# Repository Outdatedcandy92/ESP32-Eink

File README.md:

# ESP32 E-INK Board

A tiny E-Ink display driver board featuring an ESP32-C3 and an onboard battery charging IC. It wirelessly drives a 2.13-inch E-Ink display and is designed for portable, ultra-low-power projects such as status displays, or dashboards.

---
## Schematic

---
## PCB

---
## BOM

| Name                                                                                                                                                               | Description                                                           | Quantity | Price      | Shipping   |
| ------------------------------------------------------------------------------------------------------------------------------------------------------------------ | --------------------------------------------------------------------- | -------- | ---------- | ---------- |
| PCB & Stencil                                                                                                                                                      | PCB & Stencil from JLCPCB                                             | -        | $10.10     | $8.47      |
| Componenets                                                                                                                                                        | Components from LCSC. Detailed breakdown [here](./production/bom.csv) | -        | $25.72     | $13.75     |
| [E-Ink Display](https://www.alibaba.com/product-detail/E-paper-Technology-2-13-Inch_1601018719280.html?spm=a2700.product_home_fy25.home_header.132.2ce267af3jYzDY) | E-Ink Display from Alibaba                                            | 1        | $6.76      | $9.66      |
| Sub Total                                                                                                                                                          |                                                                       |          | **$42.58** | **$31.88** |
| Total                                                                                                                                                              |                                                                       |          | **$74.46** |            |

---

## License

This project is licensed under the CERN Open Hardware Licence Version 2 Weakly Reciprocal [(CERN OHL W)](LICENSE.txt)

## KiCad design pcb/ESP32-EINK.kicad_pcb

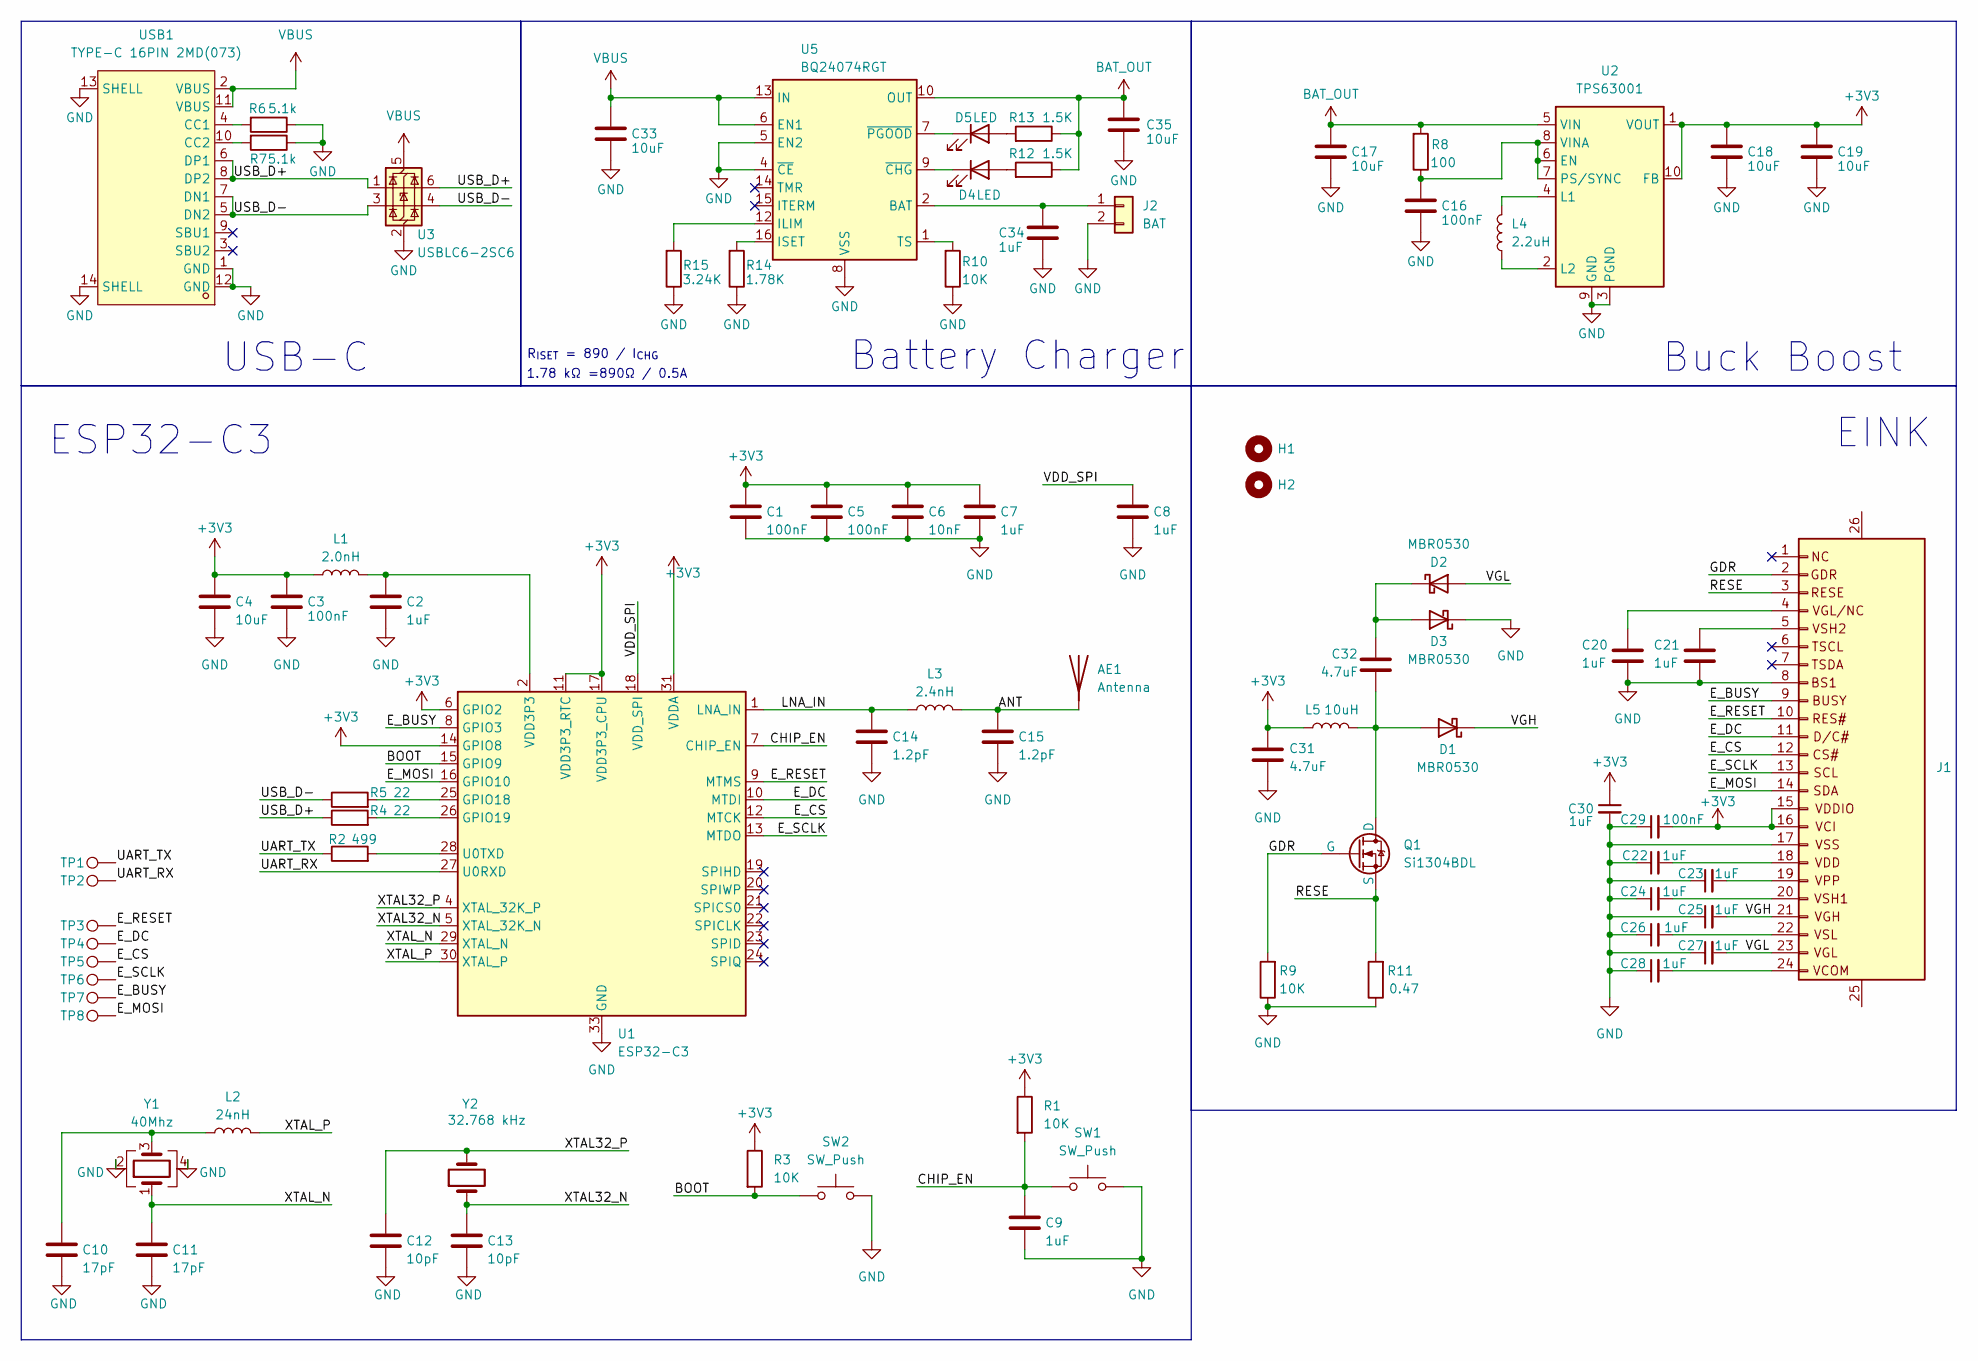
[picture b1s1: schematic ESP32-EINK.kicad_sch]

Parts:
AE1: Antenna; Johanson_2450AT18x100; LCSC Part C89334
C1, C3, C5, C16, C29: 100nF; C_0402_1005Metric; LCSC Part C1525
C2, C7, C8, C9, C20, C21, C22, C23, C24, C25, C26, C27, C28, C30, C34: 1uF; C_0402_1005Metric; LCSC Part C52923
C4, C17, C18, C19, C33, C35: 10uF; C_0402_1005Metric; LCSC Part C315248
C6: 10nF; C_0402_1005Metric; LCSC Part C15195
C10, C11: 17pF; C_0402_1005Metric; LCSC Part C1517782
C12, C13: 10pF; C_0402_1005Metric; LCSC Part C76946
C14, C15: 1.2pF; C_0201_0603Metric; LCSC Part C85895
C31, C32: 4.7uF; C_0402_1005Metric; LCSC Part C23733
D1, D2, D3: MBR0530; D_SOD-123; LCSC Part C82046
D4, D5: LED; LED_0402_1005Metric; LCSC Part C30584803
H1, H2: MountingHole; MountingHole_2.2mm_M2
J1: Conn_01x26; FPC-SMD_24P-P0.50_05B20U24P; LCSC Part C5362165
J2: BAT; JST_SH_BM02B-SRSS-TB_1x02-1MP_P1.00mm_Vertical; LCSC Part C160402
L1: 2.0nH; L_0402_1005Metric; LCSC Part C2986275
L2: 24nH; L_0402_1005Metric; LCSC Part C167472
L3: 2.4nH; L_0201_0603Metric; LCSC Part C2043647
L4: 2.2uH; L_1008_2520Metric; LCSC Part C1333325
L5: 10uH; IND-SMD_L4.0-W4.0_FNR40XXS; LCSC Part C167879
Q1: Si1304BDL; SOT-323_SC-70; LCSC Part C7419947
R1, R3, R9, R10: 10K; R_0402_1005Metric; LCSC Part C25531
R2: 499; R_0402_1005Metric; LCSC Part C4125
R4, R5: 22; R_0402_1005Metric; LCSC Part C25092
R6, R7: 5.1k; R_0402_1005Metric; LCSC Part C25905
R8: 100; R_0402_1005Metric; LCSC Part C25076
R11: 0.47; R_0402_1005Metric; LCSC Part C2771738
R12, R13: 1.5K; R_0402_1005Metric; LCSC Part C25867
R14: 1.78K; R_0402_1005Metric; LCSC Part C113478
R15: 3.24K; R_0402_1005Metric; LCSC Part C11457
SW1, SW2: SW_Push; SW-SMD_L3.9-W3.0-P4.45; LCSC Part C720477
TP1, TP2, TP3, TP4, TP5, TP6, TP7, TP8: TestPoint; TestPoint_Keystone_5000-5004_Miniature; LCSC Part C5199802
U1: ESP32-C3; QFN-32-1EP_5x5mm_P0.5mm_EP3.7x3.7mm; LCSC Part C2858491
U2: TPS63001; Texas_DRC0010J_ThermalVias; LCSC Part C28060
U3: USBLC6-2SC6; SOT-23-6; LCSC Part C7519
U5: BQ24074RGT; VQFN-16-1EP_3x3mm_P0.5mm_EP1.6x1.6mm; LCSC Part C54313
USB1: TYPE-C 16PIN 2MD(073); USB-C-SMD_TYPE-C-6PIN-2MD-073; LCSC Part C2765186
Y1: 40Mhz; Crystal_SMD_2016-4Pin_2.0x1.6mm; LCSC Part C255898
Y2: 32.768 kHz; Crystal_SMD_2012-2Pin_2.0x1.2mm; LCSC Part C99009

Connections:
+3V3: C1.1, C3.1, C4.1, C5.1, C6.1, C7.1, C18.1, C19.1, C29.2, C30.1, C31.1, J1.15, J1.16, L1.1, L5.1, R1.1, R3.1, U1.6 (GPIO2), U1.11 (VDD3P3_RTC), U1.14 (GPIO8), U1.17 (VDD3P3_CPU), U1.31 (VDDA), U1.32 (VDDA), U2.1 (VOUT), U2.10 (FB)
/ANT: AE1.1 (A), C15.1, L3.2
/BOOT: R3.2, SW2.1, U1.15 (GPIO9)
/CHIP_EN: C9.1, R1.2, SW1.1, U1.7 (CHIP_EN)
/E_BUSY: J1.9, TP7.1, U1.8 (GPIO3)
/E_CS: J1.12, TP5.1, U1.12 (MTCK)
/E_DC: J1.11, TP4.1, U1.10 (MTDI)
/E_MOSI: J1.14, TP8.1, U1.16 (GPIO10)
/E_RESET: J1.10, TP3.1, U1.9 (MTMS)
/E_SCLK: J1.13, TP6.1, U1.13 (MTDO)
/GDR: J1.2, Q1.2 (G), R9.2
/LNA_IN: C14.1, L3.1, U1.1 (LNA_IN)
/RESE: J1.3, Q1.3 (S), R11.2
/UART_RX: TP2.1, U1.27 (U0RXD)
/UART_TX: R2.1, TP1.1
/USB_D+: R4.1, U3.1 (I/O1), U3.6 (I/O1), USB1.6 (DP1), USB1.8 (DP2)
/USB_D-: R5.1, U3.3 (I/O2), U3.4 (I/O2), USB1.5 (DN2), USB1.7 (DN1)
/VDD_SPI: C8.1, U1.18 (VDD_SPI)
/VGH: C25.2, D1.1 (K), J1.21
/VGL: C27.2, D2.2 (A), J1.23
/XTAL32_N: C13.1, U1.5 (XTAL_32K_N), Y2.1
/XTAL32_P: C12.1, U1.4 (XTAL_32K_P), Y2.2
/XTAL_N: C11.1, U1.29 (XTAL_N), Y1.1
/XTAL_P: L2.2, U1.30 (XTAL_P)
BAT_OUT: C17.1, C35.1, R8.2, R12.1, R13.1, U2.5 (VIN), U5.10 (OUT), U5.11 (OUT)
GND: C1.2, C2.2, C3.2, C4.2, C5.2, C6.2, C7.2, C8.2, C9.2, C10.2, C11.2, C12.2, C13.2, C14.2, C15.2, C16.2, C17.2, C18.2, C19.2, C20.1, C21.1, C22.1, C23.1, C24.1, C25.1, C26.1, C27.1, C28.1, C29.1, C30.2, C31.2, C33.2, C34.2, C35.2, D3.1 (K), J1.8, J1.17, J2.2, R6.1, R7.1, R9.1, R10.1, R11.1, R14.1, R15.1, SW1.2, SW2.2, U1.33 (GND), U2.3 (PGND), U2.9 (GND), U2.11 (PGND), U3.2 (GND), U5.4 (~CE), U5.5 (EN2), U5.8 (VSS), U5.17 (VSS), USB1.1 (GND), USB1.12 (GND), USB1.13 (SHELL), USB1.14 (SHELL), Y1.2, Y1.4
unnamed: C2.1, L1.2, U1.2 (VDD3P3), U1.3 (VDD3P3)
unnamed: C10.1, L2.1, Y1.3
unnamed: C32.2, D1.2 (A), L5.2, Q1.1 (D)
unnamed: C32.1, D2.1 (K), D3.2 (A)
unnamed: D4.2 (A), R12.2
unnamed: D4.1 (K), U5.9 (~CHG)
unnamed: D5.2 (A), R13.2
unnamed: D5.1 (K), U5.7 (~PGOOD)
unnamed: C20.2, J1.4
unnamed: C21.2, J1.5
unnamed: C22.2, J1.18
unnamed: C23.2, J1.19
unnamed: C24.2, J1.20
unnamed: C26.2, J1.22
unnamed: C28.2, J1.24
unnamed: C34.1, J2.1, U5.2 (BAT), U5.3 (BAT)
unnamed: R5.2, U1.25 (GPIO18)
unnamed: R4.2, U1.26 (GPIO19)
unnamed: R2.2, U1.28 (U0TXD)
unnamed: C16.1, R8.1, U2.6 (EN), U2.7 (PS/SYNC), U2.8 (VINA)
unnamed: L4.2, U2.4 (L1)
unnamed: L4.1, U2.2 (L2)
unnamed: R15.2, U5.12 (ILIM)
unnamed: R14.2, U5.16 (ISET)
unnamed: R10.2, U5.1 (TS)
unnamed: R6.2, USB1.4 (CC1)
unnamed: R7.2, USB1.10 (CC2)
VBUS: C33.1, U3.5 (VBUS), U5.6 (EN1), U5.13 (IN), USB1.2 (VBUS), USB1.11 (VBUS)

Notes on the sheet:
ESP32-C3
Buck Boost
Battery Charger
1.78 kΩ =890Ω / 0.5A
R_{ISET} = 890 / I_{CHG}
USB-C
EINK

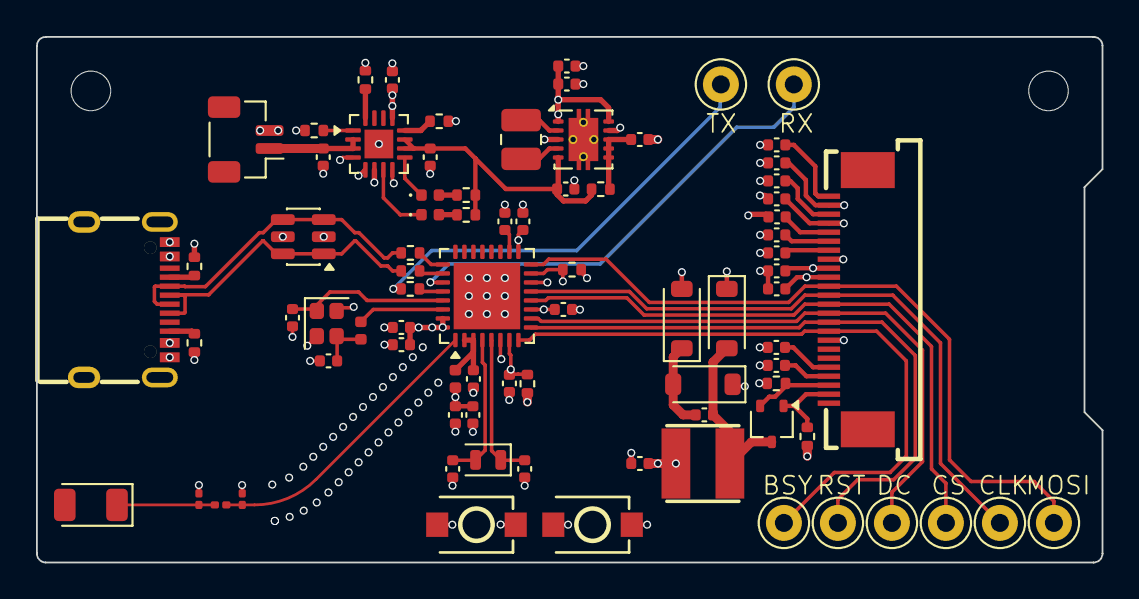
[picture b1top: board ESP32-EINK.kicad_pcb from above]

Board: 4 copper layers, 59.2 x 29.2 mm, 83 parts (0 on the bottom side), 54 nets.

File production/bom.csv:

"Reference","Qty","Footprint","Value","LCSC Part"
"AE1","1","RF_Antenna:Johanson_2450AT18x100","Antenna","C89334"
"C1,C3,C5,C16,C29","5","Capacitor_SMD:C_0402_1005Metric","100nF","C1525"
"C2,C7,C8,C9,C20,C21,C22,C23,C24,C25,C26,C27,C28,C30,C34","15","Capacitor_SMD:C_0402_1005Metric","1uF","C52923"
"C4,C17,C18,C19,C33,C35","6","Capacitor_SMD:C_0402_1005Metric","10uF","C315248"
"C6","1","Capacitor_SMD:C_0402_1005Metric","10nF","C15195"
"C10,C11","2","Capacitor_SMD:C_0402_1005Metric","17pF","C1517782"
"C12,C13","2","Capacitor_SMD:C_0402_1005Metric","10pF","C76946"
"C14,C15","2","Capacitor_SMD:C_0201_0603Metric","1.2pF","C85895"
"C31,C32","2","Capacitor_SMD:C_0402_1005Metric","4.7uF","C23733"
"D1,D2,D3","3","Diode_SMD:D_SOD-123","MBR0530","C82046"
"D4,D5","2","LED_SMD:LED_0402_1005Metric","LED","C30584803"
"H1,H2","2","MountingHole:MountingHole_2.2mm_M2","MountingHole","-"
"J1","1","easyeda2kicad:FPC-SMD_24P-P0.50_05B20U24P","Conn_01x26","C5362165"
"J2","1","Connector_JST:JST_SH_BM02B-SRSS-TB_1x02-1MP_P1.00mm_Vertical","BAT","C160402"
"L1","1","Inductor_SMD:L_0402_1005Metric","2.0nH","C2986275"
"L2","1","Inductor_SMD:L_0402_1005Metric","24nH","C167472"
"L3","1","Inductor_SMD:L_0201_0603Metric","2.4nH","C2043647"
"L4","1","Inductor_SMD:L_1008_2520Metric","2.2uH","C1333325"
"L5","1","easyeda2kicad:IND-SMD_L4.0-W4.0_FNR40XXS","10uH","C167879"
"Q1","1","Package_TO_SOT_SMD:SOT-323_SC-70","Si1304BDL","C7419947"
"R1,R3,R9,R10","4","Resistor_SMD:R_0402_1005Metric","10K","C25531"
"R2","1","Resistor_SMD:R_0402_1005Metric","499","C4125"
"R4,R5","2","Resistor_SMD:R_0402_1005Metric","22","C25092"
"R6,R7","2","Resistor_SMD:R_0402_1005Metric","5.1k","C25905"
"R8","1","Resistor_SMD:R_0402_1005Metric","100","C25076"
"R11","1","Resistor_SMD:R_0402_1005Metric","0.47","C2771738"
"R12,R13","2","Resistor_SMD:R_0402_1005Metric","1.5K","C25867"
"R14","1","Resistor_SMD:R_0402_1005Metric","1.78K","C113478"
"R15","1","Resistor_SMD:R_0402_1005Metric","3.24K","C11457"
"SW1,SW2","2","easyeda2kicad:SW-SMD_L3.9-W3.0-P4.45","SW_Push","C720477"
"TP1,TP2,TP3,TP4,TP5,TP6,TP7,TP8","8","TestPoint:TestPoint_Keystone_5000-5004_Miniature","TestPoint","C5199802"
"U1","1","Package_DFN_QFN:QFN-32-1EP_5x5mm_P0.5mm_EP3.7x3.7mm","ESP32-C3","C2858491"
"U2","1","Package_SON:Texas_DRC0010J_ThermalVias","TPS63001","C28060"
"U3","1","Package_TO_SOT_SMD:SOT-23-6","USBLC6-2SC6","C7519"
"U5","1","Package_DFN_QFN:VQFN-16-1EP_3x3mm_P0.5mm_EP1.6x1.6mm","BQ24074RGT","C54313"
"USB1","1","easyeda2kicad:USB-C-SMD_TYPE-C-6PIN-2MD-073","TYPE-C 16PIN 2MD(073)","C2765186"
"Y1","1","Crystal:Crystal_SMD_2016-4Pin_2.0x1.6mm","40Mhz","C255898"
"Y2","1","Crystal:Crystal_SMD_2012-2Pin_2.0x1.2mm","32.768 kHz","C99009"

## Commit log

2025-12-31 Day 2
2026-01-11 rev 1
2026-02-01 readme update
2026-02-01 bom update
2026-02-13 placeholder code
